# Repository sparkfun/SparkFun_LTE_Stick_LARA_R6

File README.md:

SparkFun LTE Stick - LARA-R6
========================================

[*SparkFun LTE Stick - LARA-R6 (CEL-23618)*](https://www.sparkfun.com/products/23618)

The SparkFun LTE Stick provides a development and prototyping platform for the LARA-R6 LTE Cat 1 module from u-blox<sup>&trade;</sup>. The LTE Stick uses the LARA-R6401 version, which supports both data and voice for North America and works with LTE bands used by these mobile networks: AT&T, Verizon, T-Mobile, and FirstNet. The board includes a nanoSIM card slot for users to select their preferred network. Check with your network provider for compatibility with the LARA-R6.

The LTE Stick routes the UART and I<sup>2</sup>S interfaces to a 0.1in.-spaced plated-through-hole (PTH) header along with the Reset and Power On signals. The board has two SMA connectors for the LARA-R6's primary and secondary antennas. The primary antenna sends and receives data, whereas the secondary antenna is receive only. Power to the board is provided either over the USB-C connector (recommended) or the VIN PTH pin (<b>6V Max</b>). The board defaults to use the higher voltage input. The board also includes test points for advanced users to solder to for the I<sup>2</sup>C interface, secondary UART, and four GPIO pins (IO1, IO2, IO3, and IO6).

Repository Contents
-------------------

* **/Documents** - Datasheets, additional product information 
* **/Examples** - Example code 
* **/Hardware** - Eagle design files (.brd, .sch)
* **/Production** - Production panel files (.brd)
* **/docs** - Documentation files for the LTE Stick - LARA-R6

Documentation
--------------

* **[Hookup Guide](https://docs.sparkfun.com/SparkFun_LTE_Stick_LARA_R6)** - Basic hookup guide for the SparkFun LTE Stick - LARA-R6.
* **[SparkFun u-blox Cellular Arduino Library](https://github.com/sparkfun/SparkFun_u-blox_Cellular_Arduino_Library)** - Arduino library for u-blox cellular modules including the LARA-R6.

Product Versions
----------------
* [CEL-23618](https://www.sparkfun.com/products/23618) - Initial release

License Information
-------------------

This product is _**open source**_! 

Please review the LICENSE.md file for license information. 

If you have any questions or concerns on licensing, please contact technical support on our [SparkFun forums](https://forum.sparkfun.com/viewforum.php?f=152).

Distributed as-is; no warranty is given.

- Your friends at SparkFun.

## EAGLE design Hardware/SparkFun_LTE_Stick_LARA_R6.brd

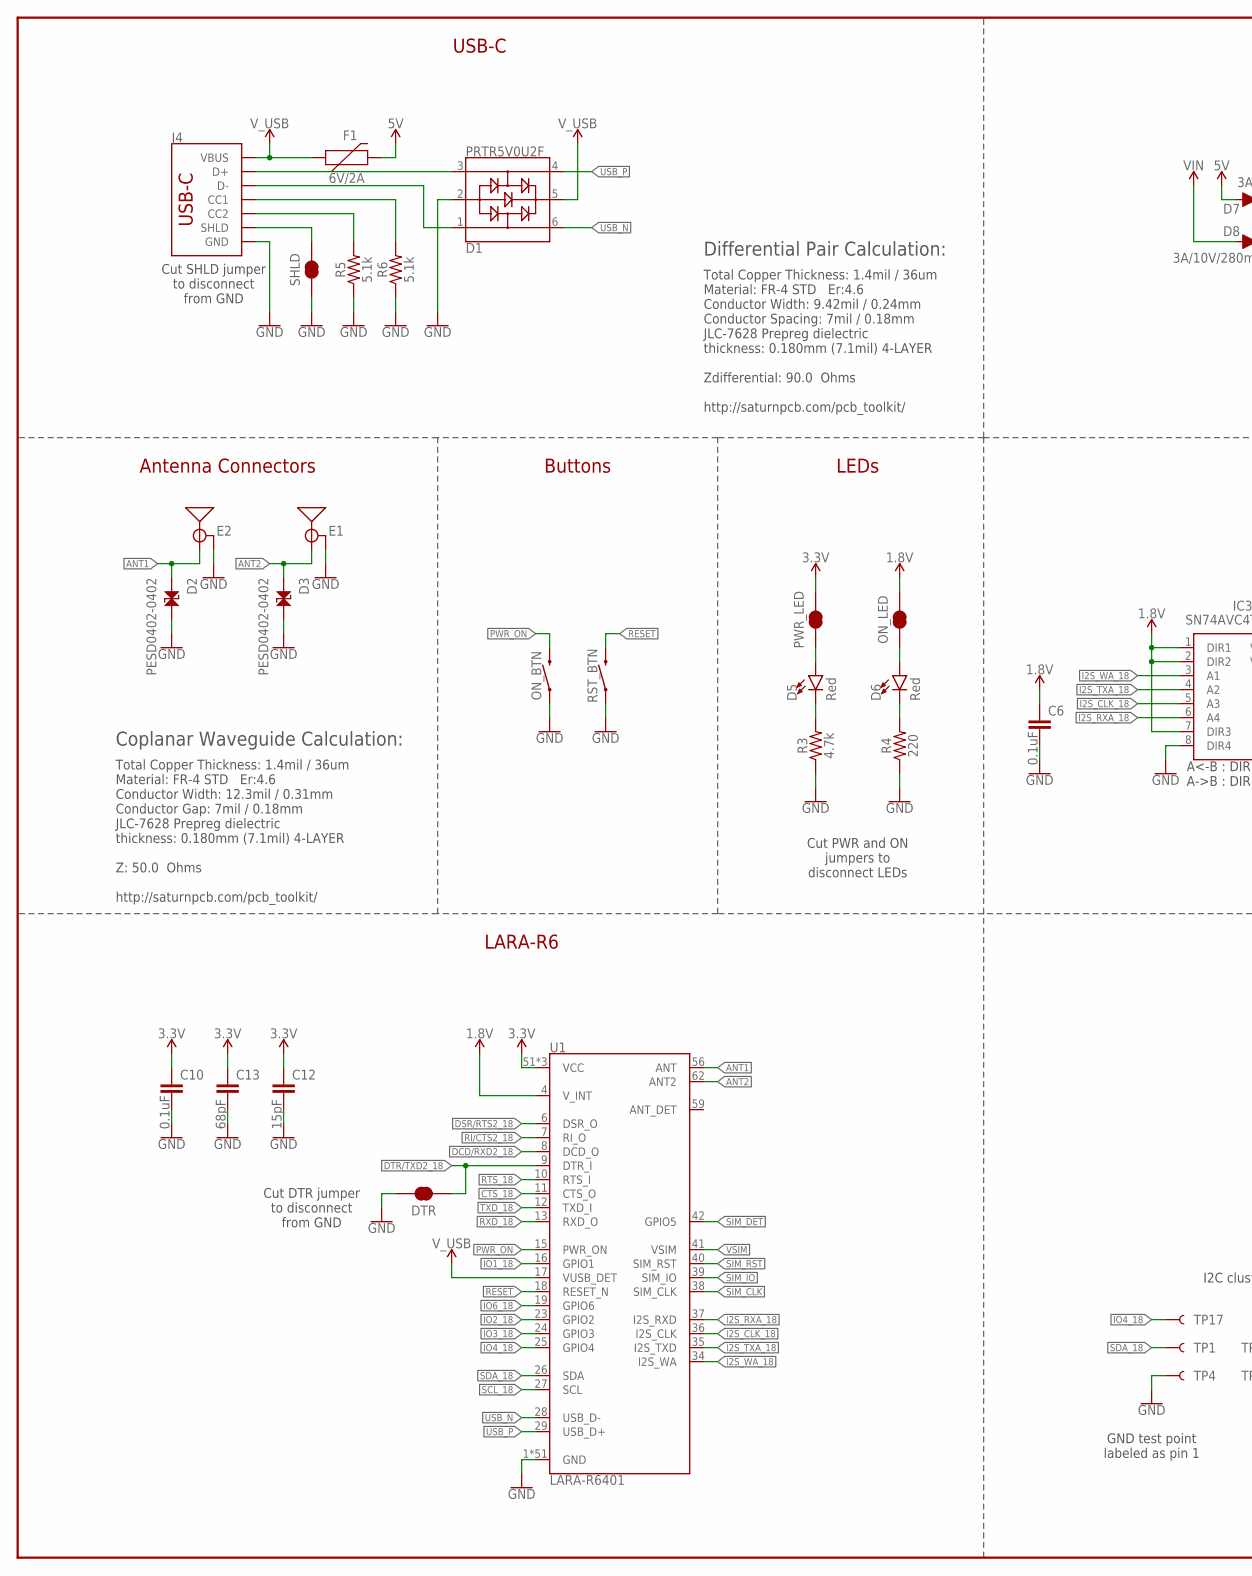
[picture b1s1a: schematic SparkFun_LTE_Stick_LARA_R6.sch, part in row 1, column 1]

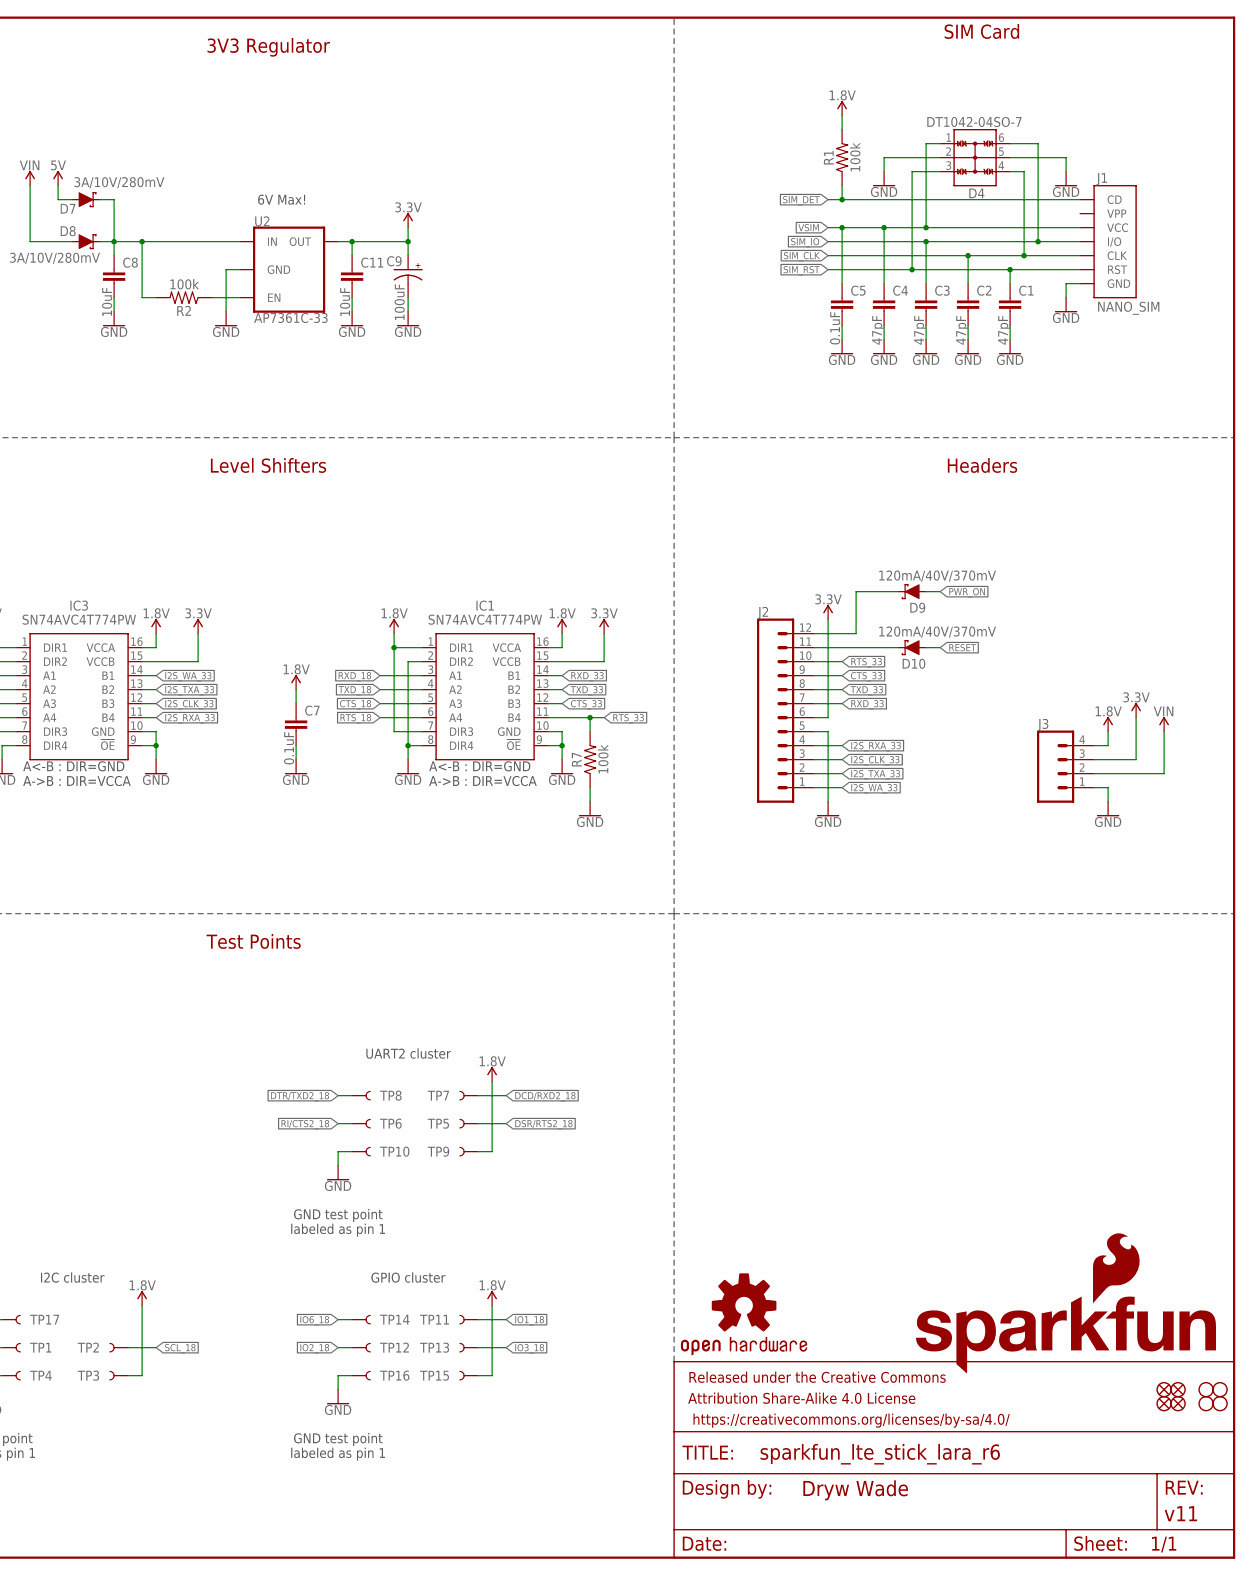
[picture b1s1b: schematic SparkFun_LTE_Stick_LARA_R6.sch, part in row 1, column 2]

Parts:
C1, C2, C3, C4: 47pF; 0603
C5, C6, C7, C10: 0.1uF; 0603
C8, C11: 10uF; 0805
C9: 100uF; PANASONIC_D
C12: 15pF; 0603
C13: 68pF; 0603
D1: PRTR5V0U2F; SOT886
D2, D3: PESD0402-0402; 0402
D4: DT1042-04SO-7; SOT23-6L
D5, D6: Red; LED-0603
D7, D8: 3A/10V/280mV; SOD-323
D9, D10: 120mA/40V/370mV; SOD-523
DTR: JUMPER-SMT_2_NC_TRACE_SILK; SMT-JUMPER_2_NC_TRACE_SILK
E1, E2: ANTENNA-SMA-GROUNDEDEDGE_SMA; SMA-EDGE
F1: 6V/2A; 1210
FD1, FD2, FD3, FD4: FIDUCIAL1X2; FIDUCIAL-1X2
FRAME1: FRAME-LEDGER; CREATIVE_COMMONS
H1, H2, H3, H4: STAND-OFF
IC1, IC3: SN74AVC4T774PW; SOP65P640X120-16N
J1: NANO_SIM; NANO_SIM_PP
J2: CONN_12NO_SILK; 1X12_NO_SILK
J3: CONN_041X04_NO_SILK_NO_POP; 1X04_NO_SILK
J4: USB_C_4-LAYER_PADS; USB-C-16P_4LAYER-PADS
LOGO1: SFE_LOGO_NAME_FLAME.1_INCH; SFE_LOGO_NAME_FLAME_.1
LOGO2: OSHW-LOGOM; OSHW-LOGO-M
ON_BTN: MOMENTARY-SWITCH-SPST-SMD-4.6X2.8MM; TACTILE_SWITCH_SMD_4.6X2.8MM
ON_LED: JUMPER-SMT_2_NC_TRACE_SILK; SMT-JUMPER_2_NC_TRACE_SILK
PWR_LED: JUMPER-SMT_2_NC_TRACE_SILK; SMT-JUMPER_2_NC_TRACE_SILK
R1, R2, R7: 100k; 0603
R3: 4.7k; 0603
R4: 220; 0603
R5, R6: 5.1k; 0603
RST_BTN: MOMENTARY-SWITCH-SPST-SMD-4.6X2.8MM; TACTILE_SWITCH_SMD_4.6X2.8MM
SHLD: JUMPER-SMT_2_NC_TRACE_SILK; SMT-JUMPER_2_NC_TRACE_SILK
TP1, TP2, TP3, TP4, TP5, TP6, TP7, TP8, TP9, TP10, TP11, TP12, TP13, TP14, TP15, TP16, TP17: TEST-POINT3X5; PAD.03X.05
U1: LARA-R6401; LARA-LGA
U2: AP7361C-33; UDFN-8

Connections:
1.8V: C6.1, C7.1, IC1.1 (DIR1), IC1.7 (DIR3), IC1.16 (VCCA), IC3.1 (DIR1), IC3.2 (DIR2), IC3.7 (DIR3), IC3.16 (VCCA), J3.4, ON_LED.2, R1.2, TP3.1, TP9.1, TP15.1, U1.4 (V_INT)
3.3V: C9.+, C10.1, C11.1, C12.1, C13.1, IC1.15 (VCCB), IC3.15 (VCCB), J2.6, J3.3, PWR_LED.2, U1.51 (VCC), U1.52 (VCC), U1.53 (VCC), U2.1 (OUT)
5V: D7.A, F1.2
!PWR_ON!: D9.A, ON_BTN.3 (2), ON_BTN.4 (2), U1.15 (PWR_ON)
!RESET!: D10.A, RST_BTN.3 (2), RST_BTN.4 (2), U1.18 (RESET_N)
ANT1: D2.1, E2.SIG (SIGNAL), U1.56 (ANT)
ANT2: D3.1, E1.SIG (SIGNAL), U1.62 (ANT2)
CTS_18: IC1.5 (A3), U1.11 (CTS_O)
CTS_33: IC1.12 (B3), J2.9
DCD/RXD2_18: TP7.1, U1.8 (DCD_O)
DSR/RTS2_18: TP5.1, U1.6 (DSR_O)
DTR/TXD2_18: DTR.2, TP8.1, U1.9 (DTR_I)
EN: R2.1, U2.5 (EN)
GND: C1.2, C2.2, C3.2, C4.2, C5.2, C6.2, C7.2, C8.2, C9.-, C10.2, C11.2, C12.2, C13.2, D1.2, D2.2, D3.2, D4.2, D4.5, DTR.1, E1.GND@0 (GND), E1.GND@1 (GND), E1.GND@2 (GND), E1.GND@3 (GND), E2.GND@0 (GND), E2.GND@1 (GND), E2.GND@2 (GND), E2.GND@3 (GND), IC1.2 (DIR2), IC1.8 (DIR4), IC1.9 (!OE), IC1.10 (GND), IC3.8 (DIR4), IC3.9 (!OE), IC3.10 (GND), J1.A1 (GND), J1.A2 (GND), J1.A3 (GND), J1.A4 (GND), J1.C5 (GND), J2.5, J3.1, J4.GND, J4.GND2 (GND), ON_BTN.1, ON_BTN.2 (1), R3.1, R4.1, R5.1, R6.1, R7.1, RST_BTN.1, RST_BTN.2 (1), SHLD.1, TP4.1, TP10.1, TP16.1, U1.1 (GND), U1.3 (GND), U1.5 (GND), U1.14 (GND), U1.20 (GND), U1.21 (GND), U1.22 (GND), U1.30 (GND), U1.32 (GND), U1.43 (GND), U1.50 (GND), U1.54 (GND), U1.55 (GND), U1.57 (GND), U1.58 (GND), U1.60 (GND), U1.61 (GND), U1.63 (GND), U1.64 (GND), U1.65 (GND), U1.66 (GND), U1.67 (GND), U1.68 (GND), U1.69 (GND), U1.70 (GND), U1.71 (GND), U1.72 (GND), U1.73 (GND), U1.74 (GND), U1.75 (GND), U1.76 (GND), U1.77 (GND), U1.78 (GND), U1.79 (GND), U1.80 (GND), U1.81 (GND), U1.82 (GND), U1.83 (GND), U1.84 (GND), U1.85 (GND), U1.86 (GND), U1.87 (GND), U1.88 (GND), U1.89 (GND), U1.90 (GND), U1.91 (GND), U1.92 (GND), U1.93 (GND), U1.94 (GND), U1.95 (GND), U1.96 (GND), U2.4 (GND), U2.EP (GND)
I2S_CLK_18: IC3.5 (A3), U1.36 (I2S_CLK)
I2S_CLK_33: IC3.12 (B3), J2.3
I2S_RXA_18: IC3.6 (A4), U1.37 (I2S_RXD)
I2S_RXA_33: IC3.11 (B4), J2.4
I2S_TXA_18: IC3.4 (A2), U1.35 (I2S_TXD)
I2S_TXA_33: IC3.13 (B2), J2.2
I2S_WA_18: IC3.3 (A1), U1.34 (I2S_WA)
I2S_WA_33: IC3.14 (B1), J2.1
IO1_18: TP11.1, U1.16 (GPIO1)
IO2_18: TP12.1, U1.23 (GPIO2)
IO3_18: TP13.1, U1.24 (GPIO3)
IO4_18: TP17.1, U1.25 (GPIO4)
IO6_18: TP14.1, U1.19 (GPIO6)
unnamed: D5.C, R3.2
unnamed: D5.A, PWR_LED.1
unnamed: D6.A, ON_LED.1
unnamed: D6.C, R4.2
unnamed: D10.C, J2.11
unnamed: D9.C, J2.12
unnamed: C8.1, D7.C, D8.C, R2.2, U2.8 (IN)
unnamed: J4.B5 (CC2), R5.2
unnamed: J4.A5 (CC1), R6.2
unnamed: D1.3, J4.A6 (D+), J4.B6 (D+)
unnamed: D1.1, J4.A7 (D-), J4.B7 (D-)
RI/CTS2_18: TP6.1, U1.7 (RI_O)
RTS_18: IC1.6 (A4), U1.10 (RTS_I)
RTS_33: IC1.11 (B4), J2.10, R7.2
RXD_18: IC1.3 (A1), U1.13 (RXD_O)
RXD_33: IC1.14 (B1), J2.7
SCL_18: TP2.1, U1.27 (SCL)
SDA_18: TP1.1, U1.26 (SDA)
SHLD: J4.SHLD1 (SHLD), J4.SHLD2 (SHLD), J4.SHLD3 (SHLD), J4.SHLD4 (SHLD), SHLD.2
SIM_CLK: C2.1, D4.4, J1.C3 (CLK), U1.38 (SIM_CLK)
SIM_DET: J1.CD, R1.1, U1.42 (GPIO5)
SIM_IO: C3.1, D4.6, J1.C7 (I/O), U1.39 (SIM_IO)
SIM_RST: C1.1, D4.3, J1.C2 (RST), U1.40 (SIM_RST)
TXD_18: IC1.4 (A2), U1.12 (TXD_I)
TXD_33: IC1.13 (B2), J2.8
USB_N: D1.6, U1.28 (USB_D-)
USB_P: D1.4, U1.29 (USB_D+)
VIN: D8.A, J3.2
VSIM: C4.1, C5.1, D4.1, J1.C1 (VCC), U1.41 (VSIM)
V_USB: D1.5, F1.1, J4.VBUS1 (VBUS), J4.VBUS2 (VBUS), U1.17 (VUSB_DET)

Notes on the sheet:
USB-C
LARA-R6
Test Points
Headers
3V3 Regulator
SIM Card
Antenna Connectors
Level Shifters
Buttons
LEDs
Cut PWR and ON jumpers to disconnect LEDs
Cut SHLD jumper to disconnect from GND
Cut DTR jumper to disconnect from GND
6V Max!
GND test point labeled as pin 1
I2C cluster
GPIO cluster
UART2 cluster
Differential Pair Calculation:
Total Copper Thickness: 1.4mil / 36um Material: FR-4 STD Er:4.6 Conductor Width: 9.42mil / 0.24mm Conductor Spacing: 7mil / 0.18mm JLC-7628 Prepreg dielectric thickness: 0.180mm (7.1mil) 4-LAYER Zdifferential: 90.0 Ohms http://saturnpcb.com/pcb_toolkit/
Coplanar Waveguide Calculation:
Total Copper Thickness: 1.4mil / 36um Material: FR-4 STD Er:4.6 Conductor Width: 12.3mil / 0.31mm Conductor Gap: 7mil / 0.18mm JLC-7628 Prepreg dielectric thickness: 0.180mm (7.1mil) 4-LAYER Z: 50.0 Ohms http://saturnpcb.com/pcb_toolkit/

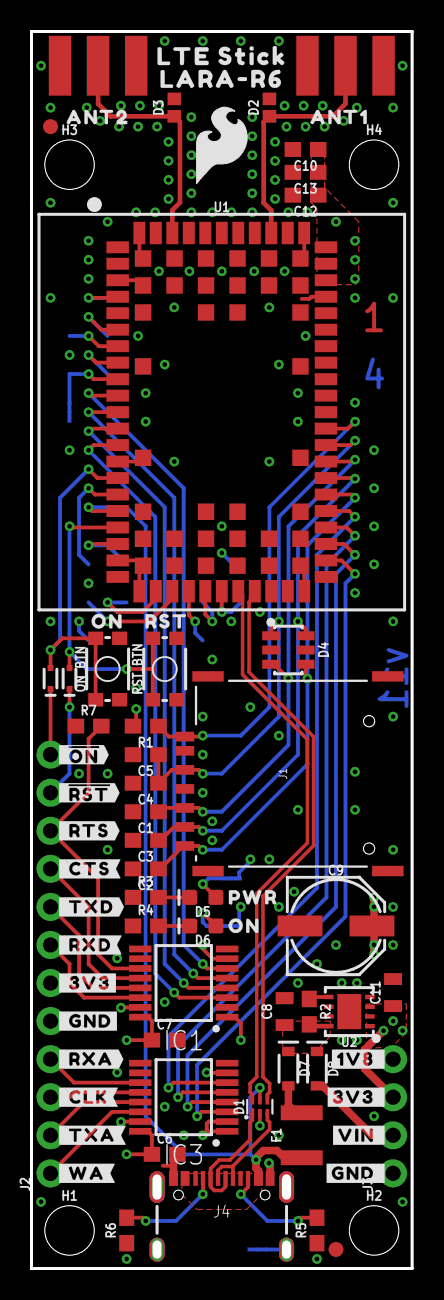
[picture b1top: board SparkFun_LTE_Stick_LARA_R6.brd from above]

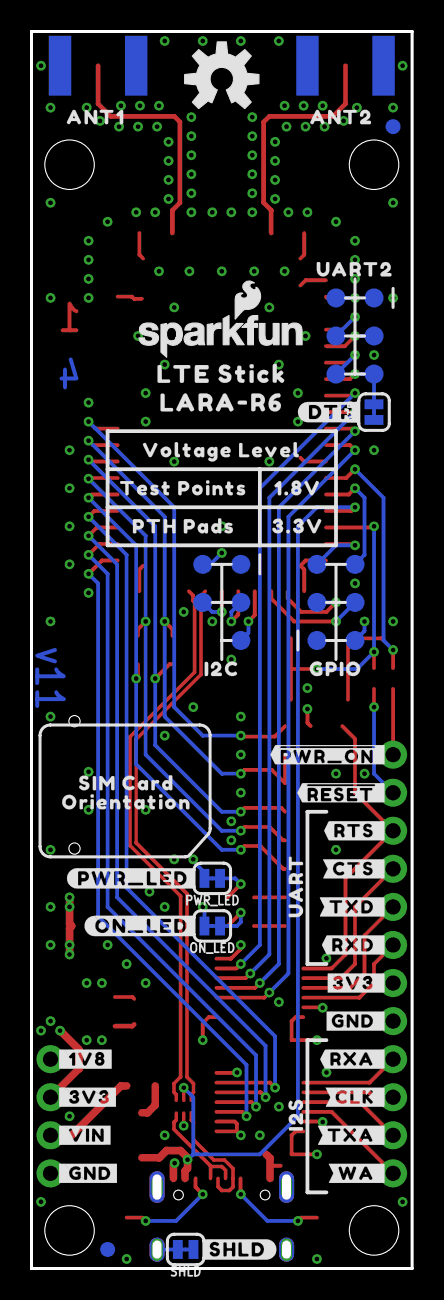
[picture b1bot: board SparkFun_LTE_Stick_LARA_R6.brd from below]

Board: 4 copper layers, 25.4 x 82.5 mm, 137 parts (61 on the bottom side), 57 nets.

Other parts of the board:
U$1, U$25: LTE_STICK0
U$2: SFE_LOGO_FLAME_.2
U$3, U$15: #_3V3#0
U$4, U$5: #_GND#0
U$6: #SHLD#0
U$7, U$8: #GND_#0
U$9, U$12: #3V3_#0
U$10: #DTR#0
U$11: #VIN_#0
U$13: #1V8_#0
U$14: #_1V8#0
U$16: #_VIN#0
U$17: #_CTS#0
U$18: #_RTS#0
U$19: #RXD_#0
U$20: #TXD_#0
U$21: #_CLK#0
U$22: #_WA#0
U$23: #RXA_#0
U$24: #TXA_#0
U$26: SIM_CARD0
U$27: VOLTAGE_LEVEL0
U$28: PWR0
U$29, U$36: ANT10
U$30: TEST_POINTS0
U$31, U$35: LARA#R60
U$32: #_RXA#0
U$33: #_#RST##0
U$34: PTH_PADS0
U$37, U$39: ON0
U$38: ##PWR_ON#_#0
U$40: #_TXA#0
U$41: #_TXD#0
U$42: #_RXD#0
U$43: #CLK_#0
U$44: #WA_#0
U$45: #RTS_#0
U$46: #CTS_#0
U$47: ##RESET#_#0
U$48: UART0
U$49: I2S0
U$50: 1#8V0
U$51: ORIENTATION0
U$52: RST0
U$53: #ON_LED#0
U$54: 3#3V0
U$55: ORDERING_INSTRUCTIONS
U$56: UART20
U$57: GPIO0
U$58: I2C0
U$59: #_#ON##0
U$60: #PWR_LED#0
U$61, U$62: ANT20

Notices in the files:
parts and their libraries:
SparkFun-Connectors: Licensing: Creative Commons ShareAlike 4.0 International - https://creativecommons.org/licenses/by-sa/4.0
SparkFun-Aesthetics: Released under the Creative Commons Attribution Share-Alike 4.0 License
SparkFun-Aesthetics: https://creativecommons.org/licenses/by-sa/4.0
